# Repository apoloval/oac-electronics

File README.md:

# Open Airbus Cockpit - Electronics

In this repository you will find designs of [Open Airbus Cockpit][1] electronic 
devices. That includes the schematics and PCB designs of panel and auxiliary
boards that, combined with Arduino platform, implements the physical logic
of the aircraft. 

## How to use it

Everything is designed with [KiCad][2]. You have to use such application
to open the files in this repository. 

## Contents

* [OAC Arduino Breakout Shield](./arduino-breakout). A shield that provides a pin breakout for Arduino mega. 
* [OAC Power Distribution Board](./power-board). A board that distributes electrical power from a PC power supply unit to the different modules of your cockpit.

[1]: http://www.openairbuscockpit.org/
[2]: http://kicad-pcb.org/

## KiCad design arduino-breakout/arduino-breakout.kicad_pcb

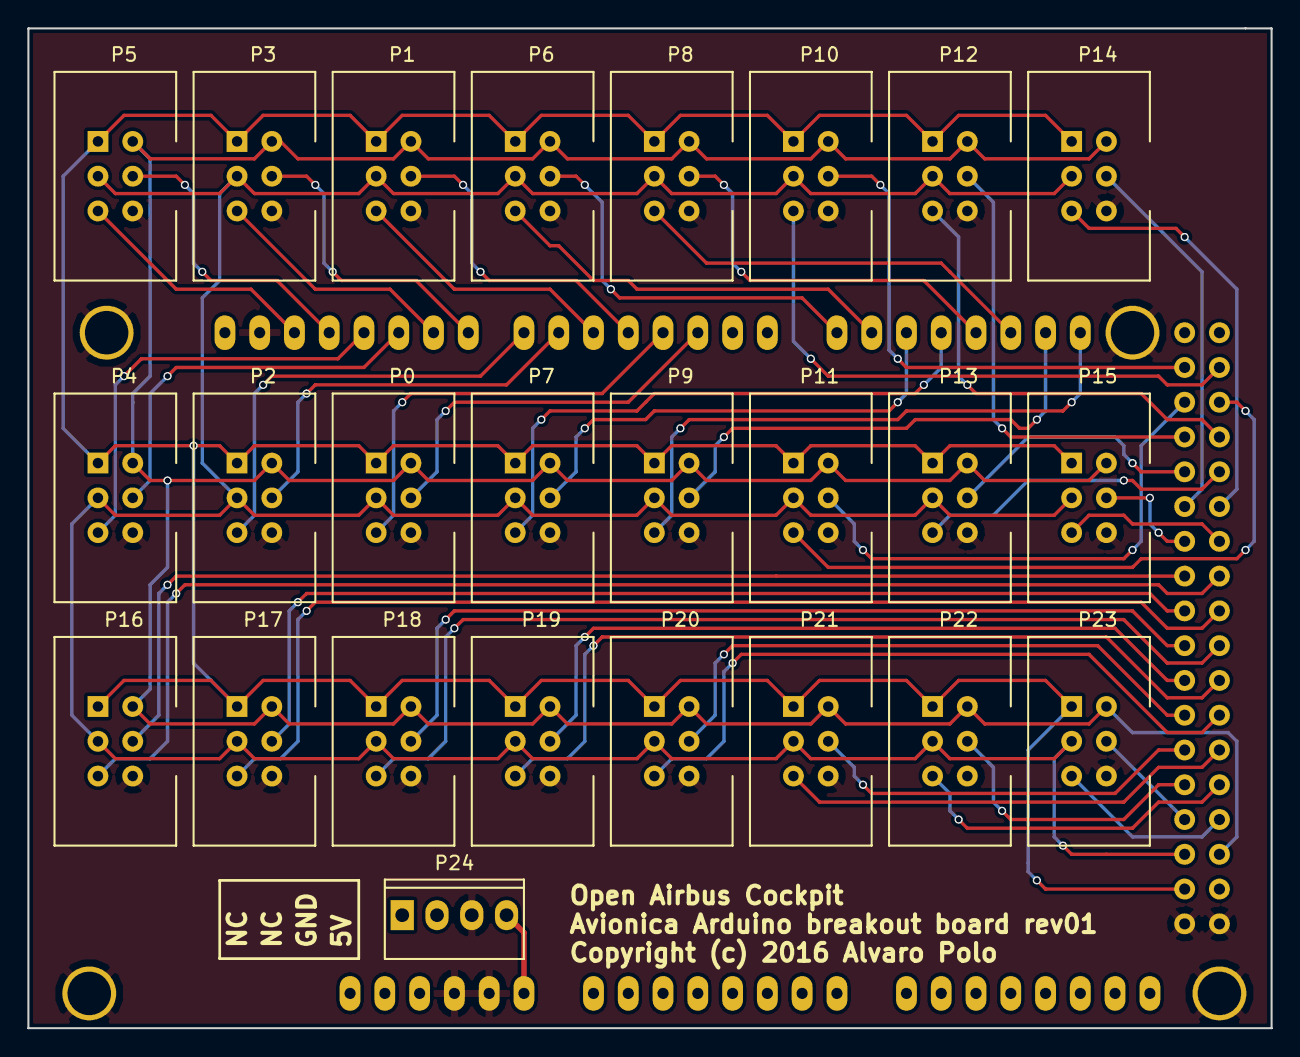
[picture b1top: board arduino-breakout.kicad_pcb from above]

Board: 2 copper layers, 90.8 x 73.0 mm, 26 parts (0 on the bottom side), 53 nets.

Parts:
P0, P1, P2, P3, P4, P5, P6, P7, P8, P9, P10, P11, P12, P13, P14, P15, P16, P17, P18, P19, P20, P21, P22, P23: CONN_01X06; idc-6p
P24: CONN_01X04; kf2510-4p
SHIELD1: ARDUINO_MEGA_SHIELD; arduino-mega-shield

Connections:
DEV0_SR: P0.5, SHIELD1.3
DEV0_SS: P0.4, SHIELD1.2
DEV1_SR: P1.5, SHIELD1.5
DEV1_SS: P1.4, SHIELD1.4
DEV2_SR: P2.5, SHIELD1.7
DEV2_SS: P2.4, SHIELD1.6
DEV3_SR: P3.5, SHIELD1.9
DEV3_SS: P3.4, SHIELD1.8
DEV4_SR: P4.5, SHIELD1.11
DEV4_SS: P4.4, SHIELD1.10
DEV5_SR: P5.5, SHIELD1.13
DEV5_SS: P5.4, SHIELD1.12
DEV6_SR: P6.5, SHIELD1.15
DEV6_SS: P6.4, SHIELD1.14
DEV7_SR: P7.5, SHIELD1.17
DEV7_SS: P7.4, SHIELD1.16
DEV8_SR: P8.5, SHIELD1.19
DEV8_SS: P8.4, SHIELD1.18
DEV9_SR: P9.5, SHIELD1.21
DEV9_SS: P9.4, SHIELD1.20
DEV10_SR: P10.5, SHIELD1.23
DEV10_SS: P10.4, SHIELD1.22
DEV11_SR: P11.5, SHIELD1.25
DEV11_SS: P11.4, SHIELD1.24
DEV12_SR: P12.5, SHIELD1.27
DEV12_SS: P12.4, SHIELD1.26
DEV13_SR: P13.5, SHIELD1.29
DEV13_SS: P13.4, SHIELD1.28
DEV14_SR: P14.5, SHIELD1.31
DEV14_SS: P14.4, SHIELD1.30
DEV15_SR: P15.5, SHIELD1.33
DEV15_SS: P15.4, SHIELD1.32
DEV16_SR: P16.5, SHIELD1.35
DEV16_SS: P16.4, SHIELD1.34
DEV17_SR: P17.5, SHIELD1.37
DEV17_SS: P17.4, SHIELD1.36
DEV18_SR: P18.5, SHIELD1.39
DEV18_SS: P18.4, SHIELD1.38
DEV19_SR: P19.5, SHIELD1.41
DEV19_SS: P19.4, SHIELD1.40
DEV20_SR: P20.5, SHIELD1.43
DEV20_SS: P20.4, SHIELD1.42
DEV21_SR: P21.5, SHIELD1.45
DEV21_SS: P21.4, SHIELD1.44
DEV22_SR: P22.5, SHIELD1.47
DEV22_SS: P22.4, SHIELD1.46
DEV23_SR: P23.5, SHIELD1.49
DEV23_SS: P23.4, SHIELD1.48
GND: P0.6, P1.6, P2.6, P3.6, P4.6, P5.6, P6.6, P7.6, P8.6, P9.6, P10.6, P11.6, P12.6, P13.6, P14.6, P15.6, P16.6, P17.6, P18.6, P19.6, P20.6, P21.6, P22.6, P23.6, P24.3, SHIELD1.GND1, SHIELD1.GND2, SHIELD1.GND3, SHIELD1.GND4, SHIELD1.GND5
MISO: P0.3, P1.3, P2.3, P3.3, P4.3, P5.3, P6.3, P7.3, P8.3, P9.3, P10.3, P11.3, P12.3, P13.3, P14.3, P15.3, P16.3, P17.3, P18.3, P19.3, P20.3, P21.3, P22.3, P23.3, SHIELD1.50
MOSI: P0.2, P1.2, P2.2, P3.2, P4.2, P5.2, P6.2, P7.2, P8.2, P9.2, P10.2, P11.2, P12.2, P13.2, P14.2, P15.2, P16.2, P17.2, P18.2, P19.2, P20.2, P21.2, P22.2, P23.2, SHIELD1.51
SCK: P0.1, P1.1, P2.1, P3.1, P4.1, P5.1, P6.1, P7.1, P8.1, P9.1, P10.1, P11.1, P12.1, P13.1, P14.1, P15.1, P16.1, P17.1, P18.1, P19.1, P20.1, P21.1, P22.1, P23.1, SHIELD1.52
VCC: P24.4, SHIELD1.V_IN

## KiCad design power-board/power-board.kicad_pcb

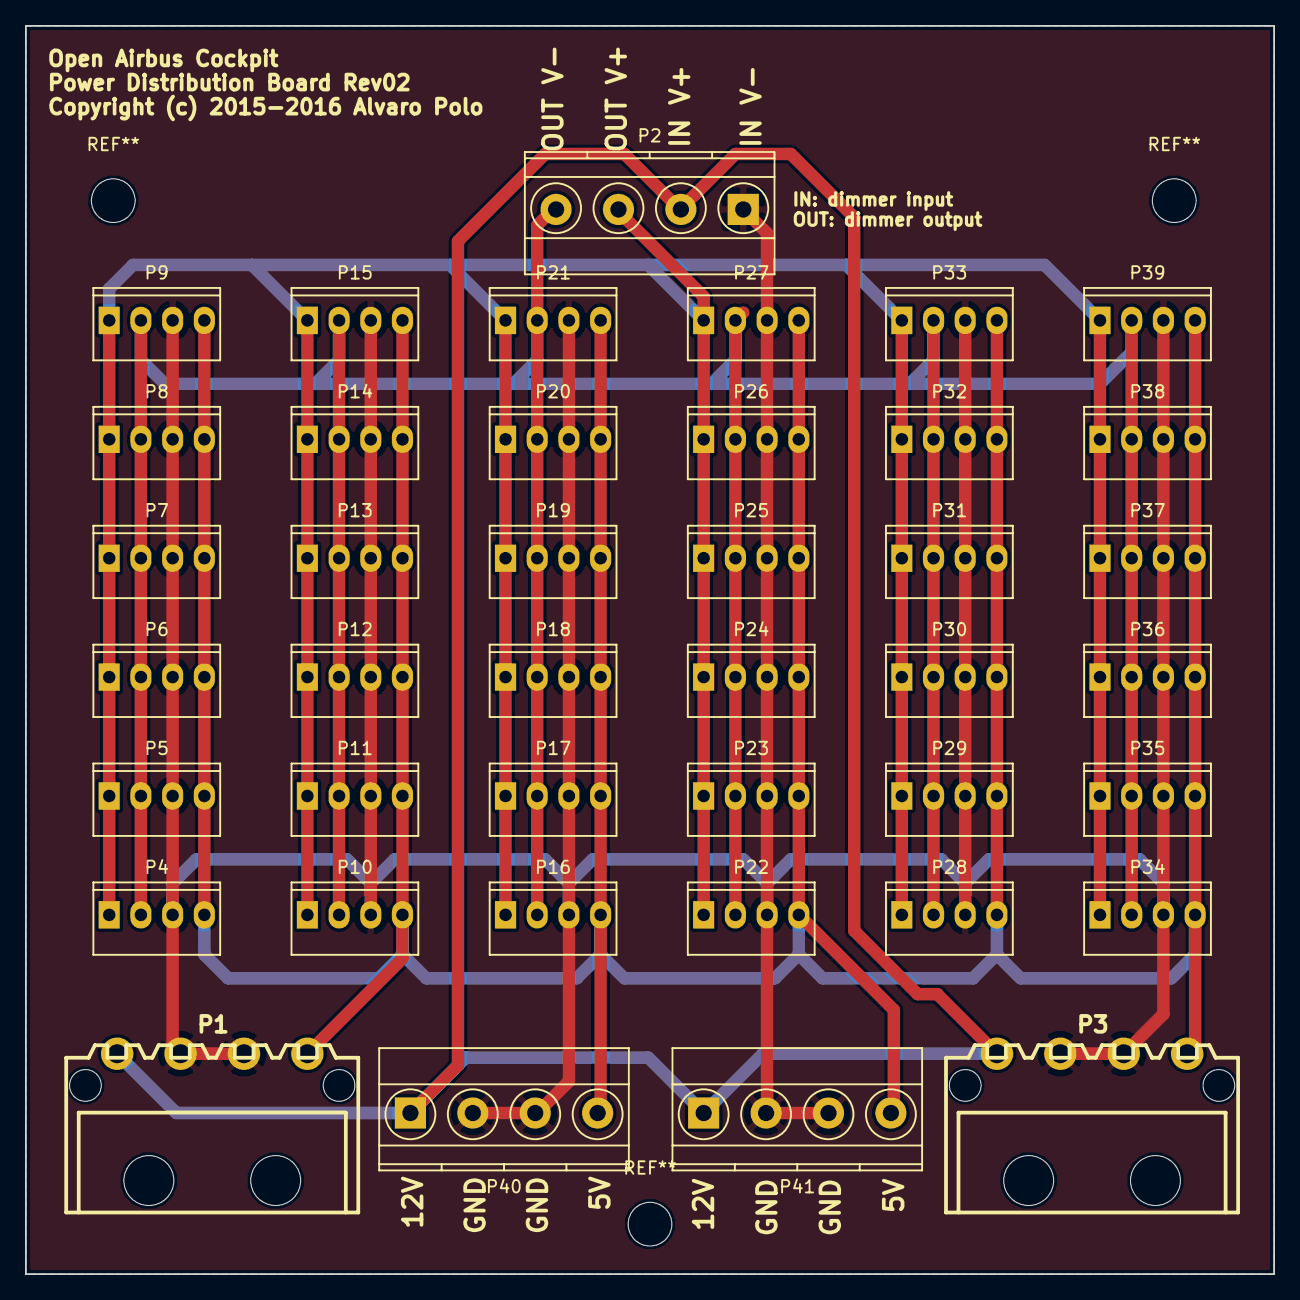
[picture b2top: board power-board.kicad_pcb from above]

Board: 2 copper layers, 100.0 x 100.0 mm, 41 parts (0 on the bottom side), 5 nets.

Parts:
P1, P3: CONN_01X04; molex-hdd
P2, P40, P41: CONN_01X04; TerminalBlock_Pheonix_MKDS1.5-4pol
P4, P5, P6, P7, P8, P9, P10, P11, P12, P13, P14, P15, P16, P17, P18, P19, P20, P21, P22, P23, P24, P25, P26, P27, P28, P29, P30, P31, P32, P33, P34, P35, P36, P37, P38, P39: CONN_01X04; kf2510-4p

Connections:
/5V: P1.4, P3.4, P4.4, P5.4, P6.4, P7.4, P8.4, P9.4, P10.4, P11.4, P12.4, P13.4, P14.4, P15.4, P16.4, P17.4, P18.4, P19.4, P20.4, P21.4, P22.4, P23.4, P24.4, P25.4, P26.4, P27.4, P28.4, P29.4, P30.4, P31.4, P32.4, P33.4, P34.4, P35.4, P36.4, P37.4, P38.4, P39.4, P40.4, P41.4
/12V: P1.1, P2.2, P3.1, P40.1, P41.1
/D12V: P2.3, P4.1, P5.1, P6.1, P7.1, P8.1, P9.1, P10.1, P11.1, P12.1, P13.1, P14.1, P15.1, P16.1, P17.1, P18.1, P19.1, P20.1, P21.1, P22.1, P23.1, P24.1, P25.1, P26.1, P27.1, P28.1, P29.1, P30.1, P31.1, P32.1, P33.1, P34.1, P35.1, P36.1, P37.1, P38.1, P39.1
/DGND: P2.4, P4.2, P5.2, P6.2, P7.2, P8.2, P9.2, P10.2, P11.2, P12.2, P13.2, P14.2, P15.2, P16.2, P17.2, P18.2, P19.2, P20.2, P21.2, P22.2, P23.2, P24.2, P25.2, P26.2, P27.2, P28.2, P29.2, P30.2, P31.2, P32.2, P33.2, P34.2, P35.2, P36.2, P37.2, P38.2, P39.2
/GND: P1.2, P1.3, P2.1, P3.2, P3.3, P4.3, P5.3, P6.3, P7.3, P8.3, P9.3, P10.3, P11.3, P12.3, P13.3, P14.3, P15.3, P16.3, P17.3, P18.3, P19.3, P20.3, P21.3, P22.3, P23.3, P24.3, P25.3, P26.3, P27.3, P28.3, P29.3, P30.3, P31.3, P32.3, P33.3, P34.3, P35.3, P36.3, P37.3, P38.3, P39.3, P40.2, P40.3, P41.2, P41.3

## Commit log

2015-03-23 So it be
2015-03-23 Add OAC Power Distribution Board designs
2015-03-23 Add a `.gitignore` file
2015-03-23 Add DesignSpark's OAC libraries
2015-03-24 Update the libraries with new components:
    * Switch on pin header
    * Rotary switch 3 on pin header
2015-03-24 Add schematic for engine start panel
2015-03-25 Add backlighting to engine start panel schematics
2015-04-08 Fix invalid holes of Molex connections in power distrib board
2015-04-08 Complete engine start panel PCB
2016-01-18 Update .gitignore file
    Include Gerber output directories in the list of things to ignore.
2016-02-18 Remove project and files from DesignSpark PCB
2016-02-18 Add basic project structure for Power Distribution Board
2016-02-20 Finalize OAC Power Board schematics
2016-02-20 Assign footprints for OAC Power Distribution Board
2016-02-20 Make Git ignore kicad net files
2016-02-20 Extend OAC power distrib from 32 to 36 connectors
2016-02-20 Make Git ignore `kicad_pcb-bak` files
2016-02-21 Add alternate screw terminals for inputs in OAC Power Board
2016-02-21 Complete OAC Power Distrib PCB
2016-02-21 Add M3 mounting holes to OAC Power Distrib board
2016-02-21 Put abs axis and prepare for plotting OAC Power Distrib
2016-02-21 Add project files for Arduino Avionica Breakout board
2016-02-21 Add initial implementation of Arduino Avionica Breakout schematics
2016-02-21 Add a power input connector to Arduino breakout board
2016-02-21 Add a new custom PCBnew library with IDC connectors
2016-02-21 Add a library for an Arduino Mega shield
2016-02-21 Add footprint libraries in Arduino breakout
2016-02-22 Complete Arduino breakout PCB
2016-02-22 Simplify Arduino mega shield library
    Move the footprint to `oac-conn`.
2016-02-22 Move KF2510 to `oac-conn`
    And reduce the dependent libraries to just that one.
2016-02-22 Complete move 3rd party modules to `oac-conn` library
2016-02-22 Normalize directory layout for Kicad libs
2016-02-22 Add 3D model for KF2510 connector
2016-02-22 Update 3D model for Molex HDD connector
2016-02-22 Add 3D model for Arduino Mega shield
2016-02-22 Add 3D model for IDC connectors
2016-02-22 Include credits file for libraries and modules
2016-02-22 Prepare Arduino breakout board rev01 for production
2016-04-29 Update README.md file

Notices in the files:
arduino-breakout/arduino-breakout.kicad_pcb:
Copyright (c) 2016 Alvaro Polo
power-board/power-board.kicad_pcb:
Copyright (c) 2015-2016 Alvaro Polo
